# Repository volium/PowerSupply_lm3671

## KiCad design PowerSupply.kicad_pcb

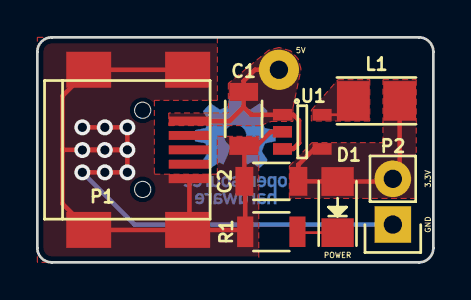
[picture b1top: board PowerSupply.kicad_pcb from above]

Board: 2 copper layers, 22.0 x 12.5 mm, 9 parts (0 on the bottom side), 5 nets.

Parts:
5V: TEST_1P; Pin_Header_Straight_1x01
C1: 10uF; C_1206
C2: 22uF; C_1206
D1: LED; LED_1206
L1: 2.2uH; Inductor_Taiyo-Yuden_NR-24xx_HandSoldering
P1: USB_OTG; USB_Mini-B
P2: CONN_01X03; Pin_Header_Straight_1x02
R1: R; R_1206
U1: LM3671MF-3.3; SOT-23-5

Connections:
+3V3: C2.1, D1.2, L1.2, P2.2, U1.4
GND: C1.2, C2.2, P1.5, P1.6, P2.1, R1.2, U1.2
unnamed: D1.1, R1.1
unnamed: L1.1, U1.5
VCC: 5V.1, C1.1, P1.1, U1.1, U1.3

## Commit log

2016-09-10 Fist commit
2016-09-12 Added MicroSD card adapter
2016-09-17 Adds Power-on LED
2016-09-19 Changes L1 with 1008 package
2016-09-19 Added updated schematic with L1 in 1008 package
2016-10-03 A lot of changes (BOM, layout, routing) Replaces inductor with footprint compatible with CDRH2D09 (Sumida) and NRH2412T (Taiyo Yuden) Removes access to 5V pin (replaced 3-pin connector with 2-pin) Up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
2016-10-05 Reduced solder mask clearance (1 mil), added fillet corner smoothing to pour areas (0.005 in)
2016-10-05 Updates orientation of Inductor (L1), and add test point for VCC)
2016-10-06 More updates to layout Reduced pad_to_mask clearance, improved solid copper areas, this version also contains OSH (Open Source Hardware) logo, available since previous commit. Added 5V, 3.3V and GND 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
2016-10-07 More cleaning up of layout Reduced clearance of top copper layer (F.Cu) GND to 0.254 mm Moved some solid copper areas to grid alignment.
2016-10-07 Adds "POWER" label to F.Mask
2016-10-10 Bumped version to v1.5 Final updates to pcb for production Updated version label (v1.5) Increased solder mask clearance to 3 mils Updated solid copper area around 5V test pin Added .gitignore file (*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
2016-10-26 Adds thermal relief to ground pin in P2 connector Bumped version 1.6, regenerated gerber files
2016-11-26 Updates value of C2 to 22 pF
2016-12-01 Moves LM3671MF-3.3 symbol to the one in volium library Stops tracking PowerSupply.bak Deletes local footprints, no longer necessary Updates .gitignore file with filters from GitHub Updates to project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
2016-12-01 Removes unnecessary fp-lib-table file
2016-12-01 Resaved project
